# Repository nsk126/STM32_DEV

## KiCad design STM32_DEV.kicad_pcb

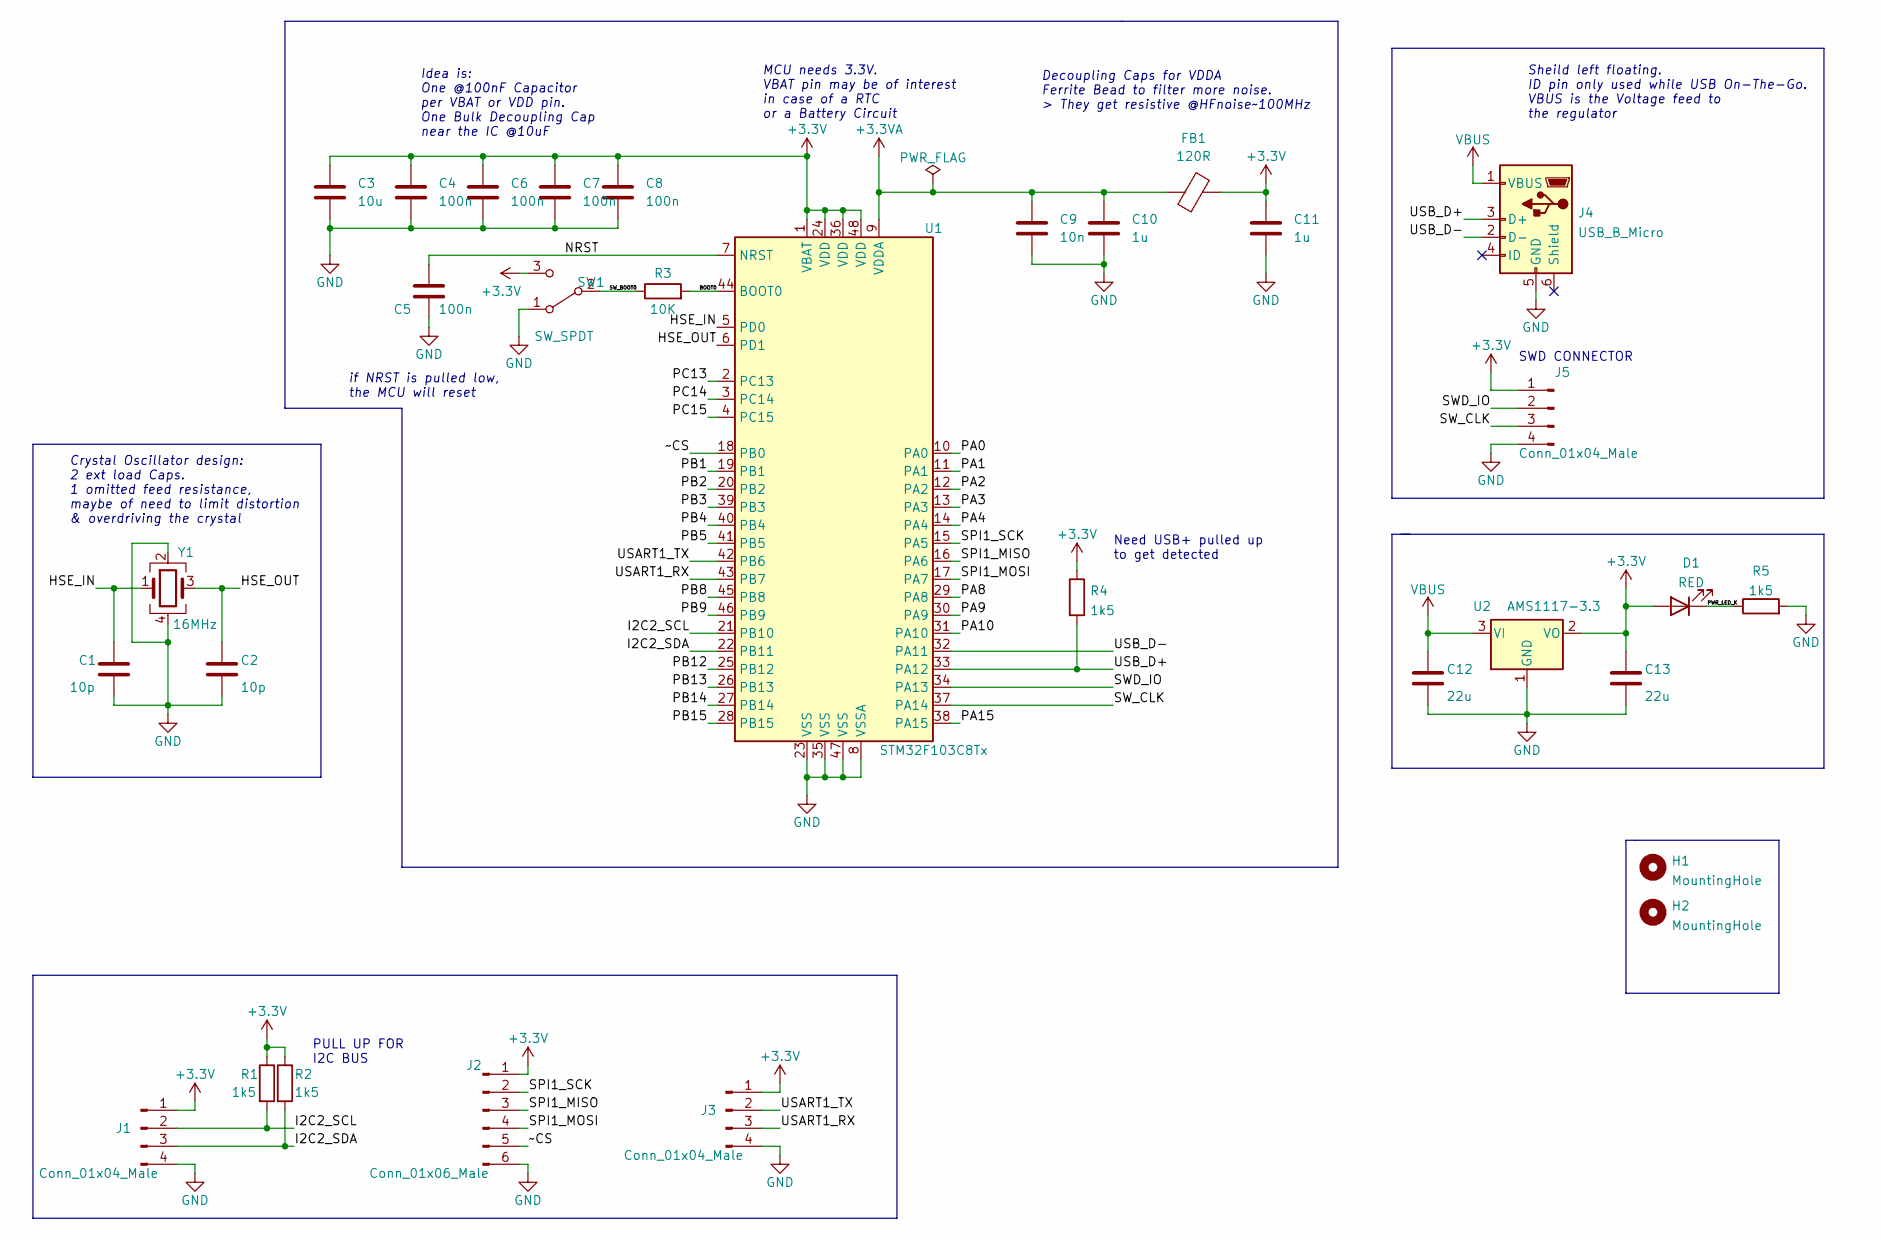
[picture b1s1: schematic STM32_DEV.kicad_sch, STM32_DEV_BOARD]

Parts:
C1, C2: 10p; C_0402_1005Metric
C3: 10u; C_0603_1608Metric
C4, C5, C6, C7, C8: 100n; C_0402_1005Metric
C9: 10n; C_0402_1005Metric
C10, C11: 1u; C_0402_1005Metric
C12, C13: 22u; C_0805_2012Metric
D1: RED; LED_0603_1608Metric
FB1: 120R; L_0603_1608Metric
H1, H2: MountingHole; MountingHole_2.2mm_M2
J1, J3, J5: Conn_01x04_Male; PinHeader_1x04_P2.54mm_Vertical
J2: Conn_01x06_Male; PinHeader_1x06_P2.54mm_Vertical
J4: USB_B_Micro; USB_Micro-B_Wuerth_629105150521
R1, R2, R4, R5: 1k5; R_0402_1005Metric
R3: 10K; R_0402_1005Metric
SW1: SW_SPDT; SW_SPDT_PCM12
U1: STM32F103C8Tx; LQFP-48_7x7mm_P0.5mm
U2: AMS1117-3.3; SOT-223-3_TabPin2
Y1: 16MHz; Crystal_SMD_3225-4Pin_3.2x2.5mm

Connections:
+3.3VA: C9.1, C10.1, FB1.1, U1.9 (VDDA)
+3V3: C3.1, C4.1, C6.1, C7.1, C8.1, C11.1, C13.1, D1.2 (A), FB1.2, J1.1, J2.1, J3.1, J5.1, R1.1, R2.1, R4.1, SW1.3 (C), U1.1 (VBAT), U1.24 (VDD), U1.36 (VDD), U1.48 (VDD), U2.2 (VO)
/BOOT0: R3.2, U1.44 (BOOT0)
/HSE_IN: C1.1, U1.5 (PD0), Y1.1
/HSE_OUT: C2.1, U1.6 (PD1), Y1.3
/I2C2_SCL: J1.2, R1.2, U1.21 (PB10)
/I2C2_SDA: J1.3, R2.2, U1.22 (PB11)
/NRST: C5.1, U1.7 (NRST)
/PA0: U1.10 (PA0)
/PA1: U1.11 (PA1)
/PA2: U1.12 (PA2)
/PA3: U1.13 (PA3)
/PA4: U1.14 (PA4)
/PA8: U1.29 (PA8)
/PA9: U1.30 (PA9)
/PA10: U1.31 (PA10)
/PA15: U1.38 (PA15)
/PB1: U1.19 (PB1)
/PB2: U1.20 (PB2)
/PB3: U1.39 (PB3)
/PB4: U1.40 (PB4)
/PB5: U1.41 (PB5)
/PB8: U1.45 (PB8)
/PB9: U1.46 (PB9)
/PB12: U1.25 (PB12)
/PB13: U1.26 (PB13)
/PB14: U1.27 (PB14)
/PB15: U1.28 (PB15)
/PC13: U1.2 (PC13)
/PC14: U1.3 (PC14)
/PC15: U1.4 (PC15)
/PWR_LED_K: D1.1 (K), R5.1
/SPI1_MISO: J2.3, U1.16 (PA6)
/SPI1_MOSI: J2.4, U1.17 (PA7)
/SPI1_SCK: J2.2, U1.15 (PA5)
/SWD_IO: J5.2, U1.34 (PA13)
/SW_BOOT0: R3.1, SW1.2 (B)
/SW_CLK: J5.3, U1.37 (PA14)
/USART1_RX: J3.3, U1.43 (PB7)
/USART1_TX: J3.2, U1.42 (PB6)
/USB_D+: J4.3 (D+), R4.2, U1.33 (PA12)
/USB_D-: J4.2 (D-), U1.32 (PA11)
/~CS: J2.5, U1.18 (PB0)
GND: C1.2, C2.2, C3.2, C4.2, C5.2, C6.2, C7.2, C8.2, C9.2, C10.2, C11.2, C12.2, C13.2, J1.4, J2.6, J3.4, J4.5 (GND), J5.4, R5.2, SW1.1 (A), U1.8 (VSSA), U1.23 (VSS), U1.35 (VSS), U1.47 (VSS), U2.1 (GND), Y1.2, Y1.4
VBUS: C12.1, J4.1 (VBUS), U2.3 (VI)

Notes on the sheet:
PULL UP FOR I2C BUS
if NRST is pulled low, the MCU will reset
Idea is: One @100nF Capacitor per VBAT or VDD pin. One Bulk Decoupling Cap near the IC @10uF
MCU needs 3.3V. VBAT pin may be of interest in case of a RTC or a Battery Circuit
Sheild left floating. ID pin only used while USB On-The-Go. VBUS is the Voltage feed to the regulator
Decoupling Caps for VDDA Ferrite Bead to filter more noise. > They get resistive @HFnoise~100MHz
Need USB+ pulled up to get detected
Crystal Oscillator design: 2 ext load Caps. 1 omitted feed resistance, maybe of need to limit distortion & overdriving the crystal
SWD CONNECTOR

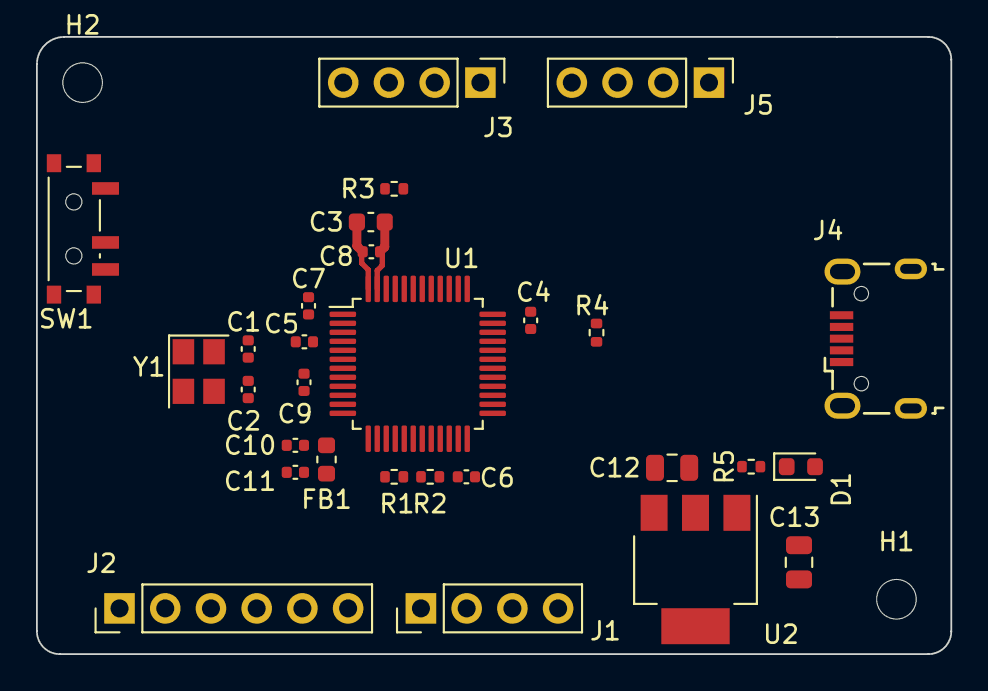
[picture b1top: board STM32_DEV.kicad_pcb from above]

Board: 2 copper layers, 50.8 x 34.3 mm, 31 parts (0 on the bottom side), 22 nets.

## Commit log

2022-02-12 init
2022-02-13 sch and pcb files udpated
2022-02-13 Delete fp-info-cache
    - wrong file
